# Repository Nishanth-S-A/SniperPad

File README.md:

# SniperPad
A wierd name for a macro pad indeed, but it means to achive its target no matter what. My goal while making this macropad was to make sure everyone can make use of my macropad. At its current state it supports windows and mac, and does great job of managing media and other utilities

## BOM:
 - 1x XIAO RP2040
 - 8x Cherry MX switches
 - 1x EC11 Rotary Encoder
 - 1x 128x32 OLED Display
 - 4x SK6812 MINI-E LEDs
 - 6x 1N4148 Diodes
 - 6x DSA keycaps
 - 4x M3x16 Bolt
 - 4x M3 Heatset

## Firmware
The firmware used here is kmk firmware. 

|  Schematic | PCB  | Case  |
| :------------ | :------------ | :------------ |
|  |  |  |

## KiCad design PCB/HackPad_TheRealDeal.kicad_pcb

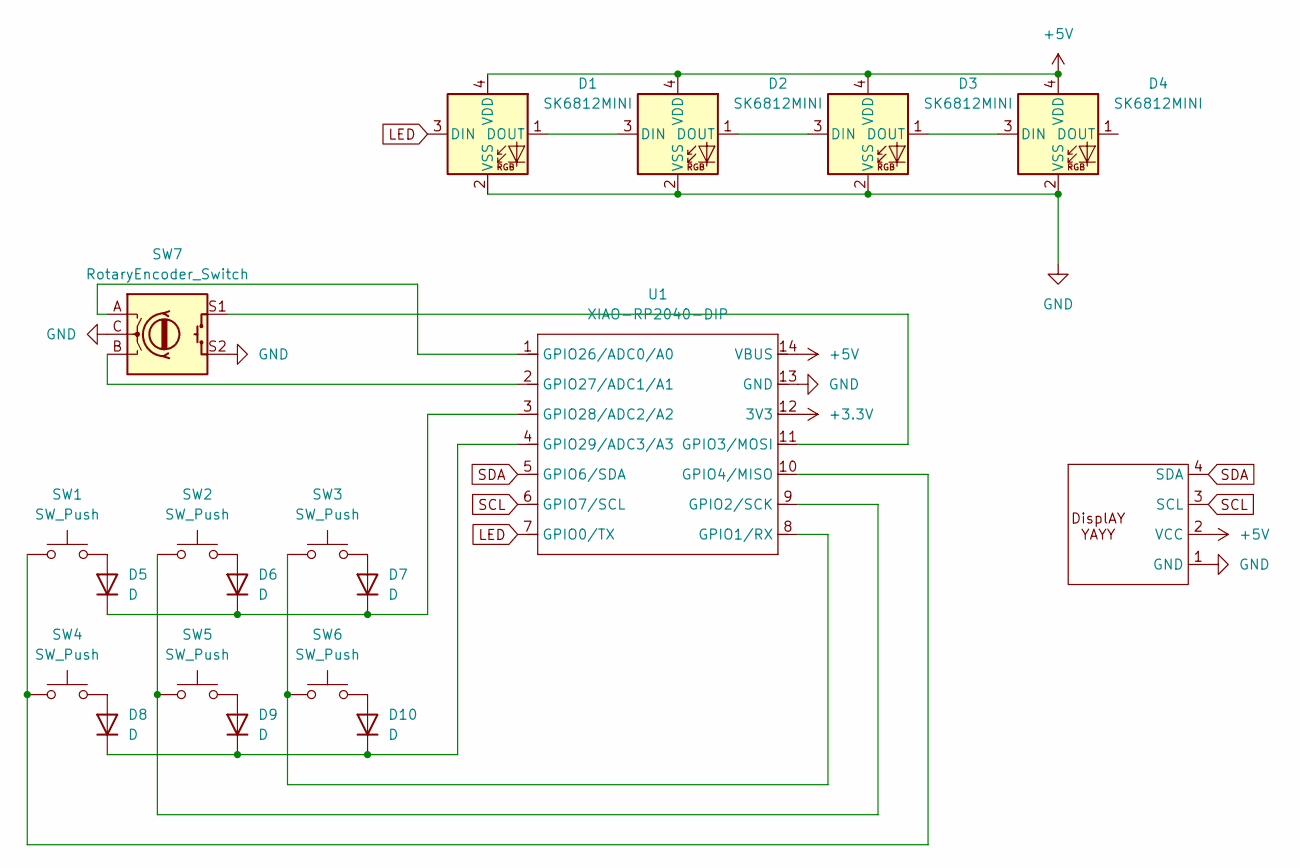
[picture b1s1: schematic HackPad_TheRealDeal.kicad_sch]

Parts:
D1, D2, D3, D4: SK6812MINI; LED_SK6812MINI_PLCC4_3.5x3.5mm_P1.75mm
D5, D6, D7, D8, D9, D10: D; D_DO-35_SOD27_P7.62mm_Horizontal
SW1, SW2, SW3, SW4, SW5, SW6: SW_Push; SW_Cherry_MX_1.00u_PCB
SW7: RotaryEncoder_Switch; RotaryEncoder_Alps_EC11E-Switch_Vertical_H20mm_CircularMoun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
U1: XIAO-RP2040-DIP
U3: SSD1306-0.91-OLED-4pin-128x32

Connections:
+3.3V: U1.12 (3V3)
+5V: D1.4 (VDD), D2.4 (VDD), D3.4 (VDD), D4.4 (VDD), U1.14 (VBUS), U3.2 (VCC)
GND: D1.2 (VSS), D2.2 (VSS), D3.2 (VSS), D4.2 (VSS), SW7.C, SW7.S2, U1.13 (GND), U3.1 (GND)
LED: D1.3 (DIN), U1.7 (GPIO0/TX)
unnamed: D1.1 (DOUT), D2.3 (DIN)
unnamed: D2.1 (DOUT), D3.3 (DIN)
unnamed: D3.1 (DOUT), D4.3 (DIN)
unnamed: D5.2 (A), SW1.2
unnamed: D5.1 (K), D6.1 (K), D7.1 (K), U1.3 (GPIO28/ADC2/A2)
unnamed: D6.2 (A), SW2.2
unnamed: D7.2 (A), SW3.2
unnamed: D8.2 (A), SW4.2
unnamed: D9.2 (A), SW5.2
unnamed: D10.2 (A), SW6.2
unnamed: D8.1 (K), D9.1 (K), D10.1 (K), U1.4 (GPIO29/ADC3/A3)
unnamed: SW3.1, SW6.1, U1.8 (GPIO1/RX)
unnamed: SW2.1, SW5.1, U1.9 (GPIO2/SCK)
unnamed: SW7.S1, U1.11 (GPIO3/MOSI)
unnamed: SW1.1, SW4.1, U1.10 (GPIO4/MISO)
unnamed: SW7.A, U1.1 (GPIO26/ADC0/A0)
unnamed: SW7.B, U1.2 (GPIO27/ADC1/A1)
SCL: U1.6 (GPIO7/SCL), U3.3 (SCL)
SDA: U1.5 (GPIO6/SDA), U3.4 (SDA)

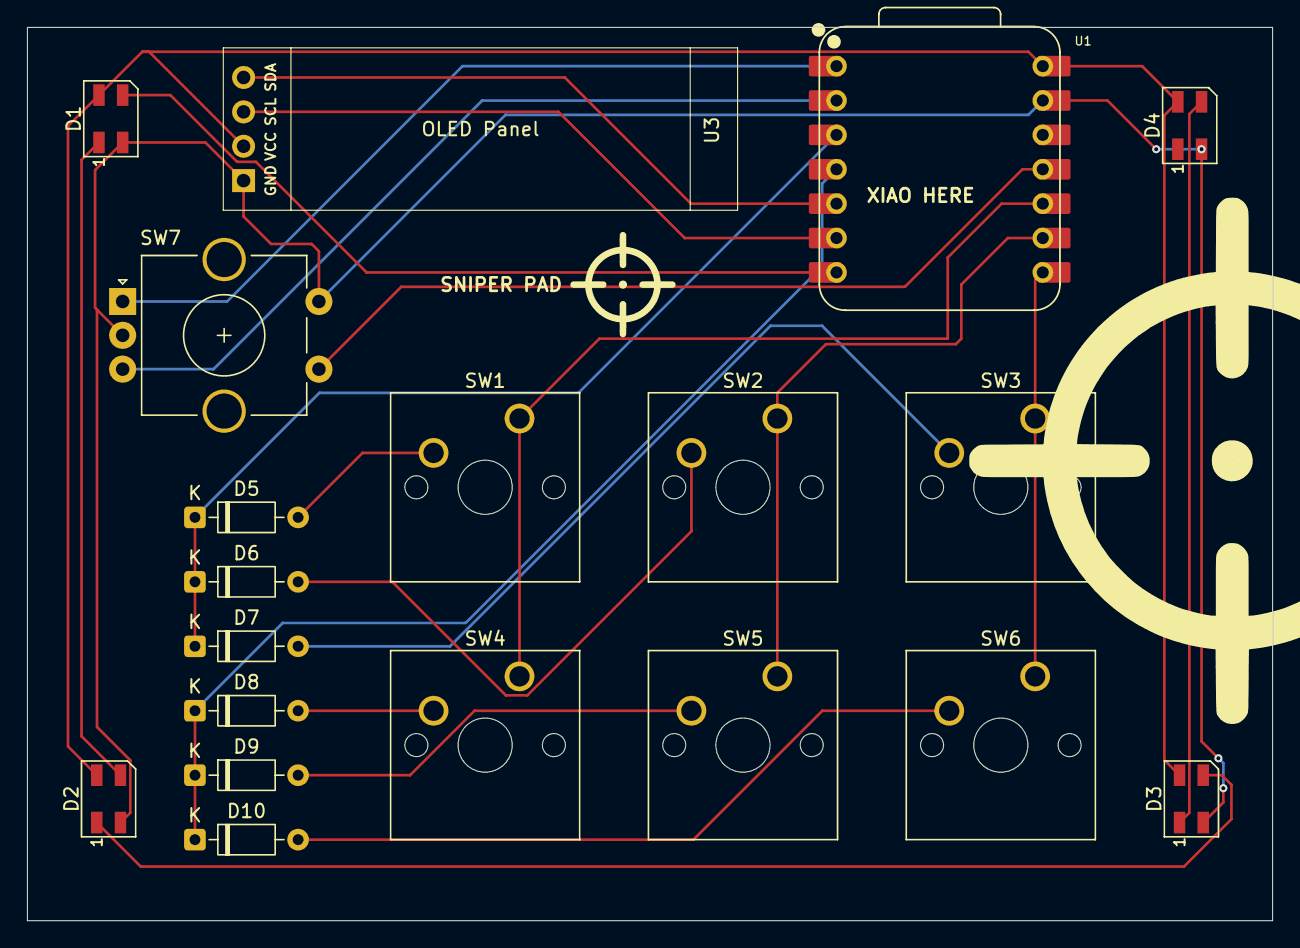
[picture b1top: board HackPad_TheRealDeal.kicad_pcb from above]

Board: 2 copper layers, 92.0 x 66.0 mm, 19 parts (0 on the bottom side), 22 nets.

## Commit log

2025-07-25 Added Cad and Firmware
2025-07-25 Added Pcb and Production files
2025-07-25 Deleted unwanted files
2025-08-07 Added firmware file to production
